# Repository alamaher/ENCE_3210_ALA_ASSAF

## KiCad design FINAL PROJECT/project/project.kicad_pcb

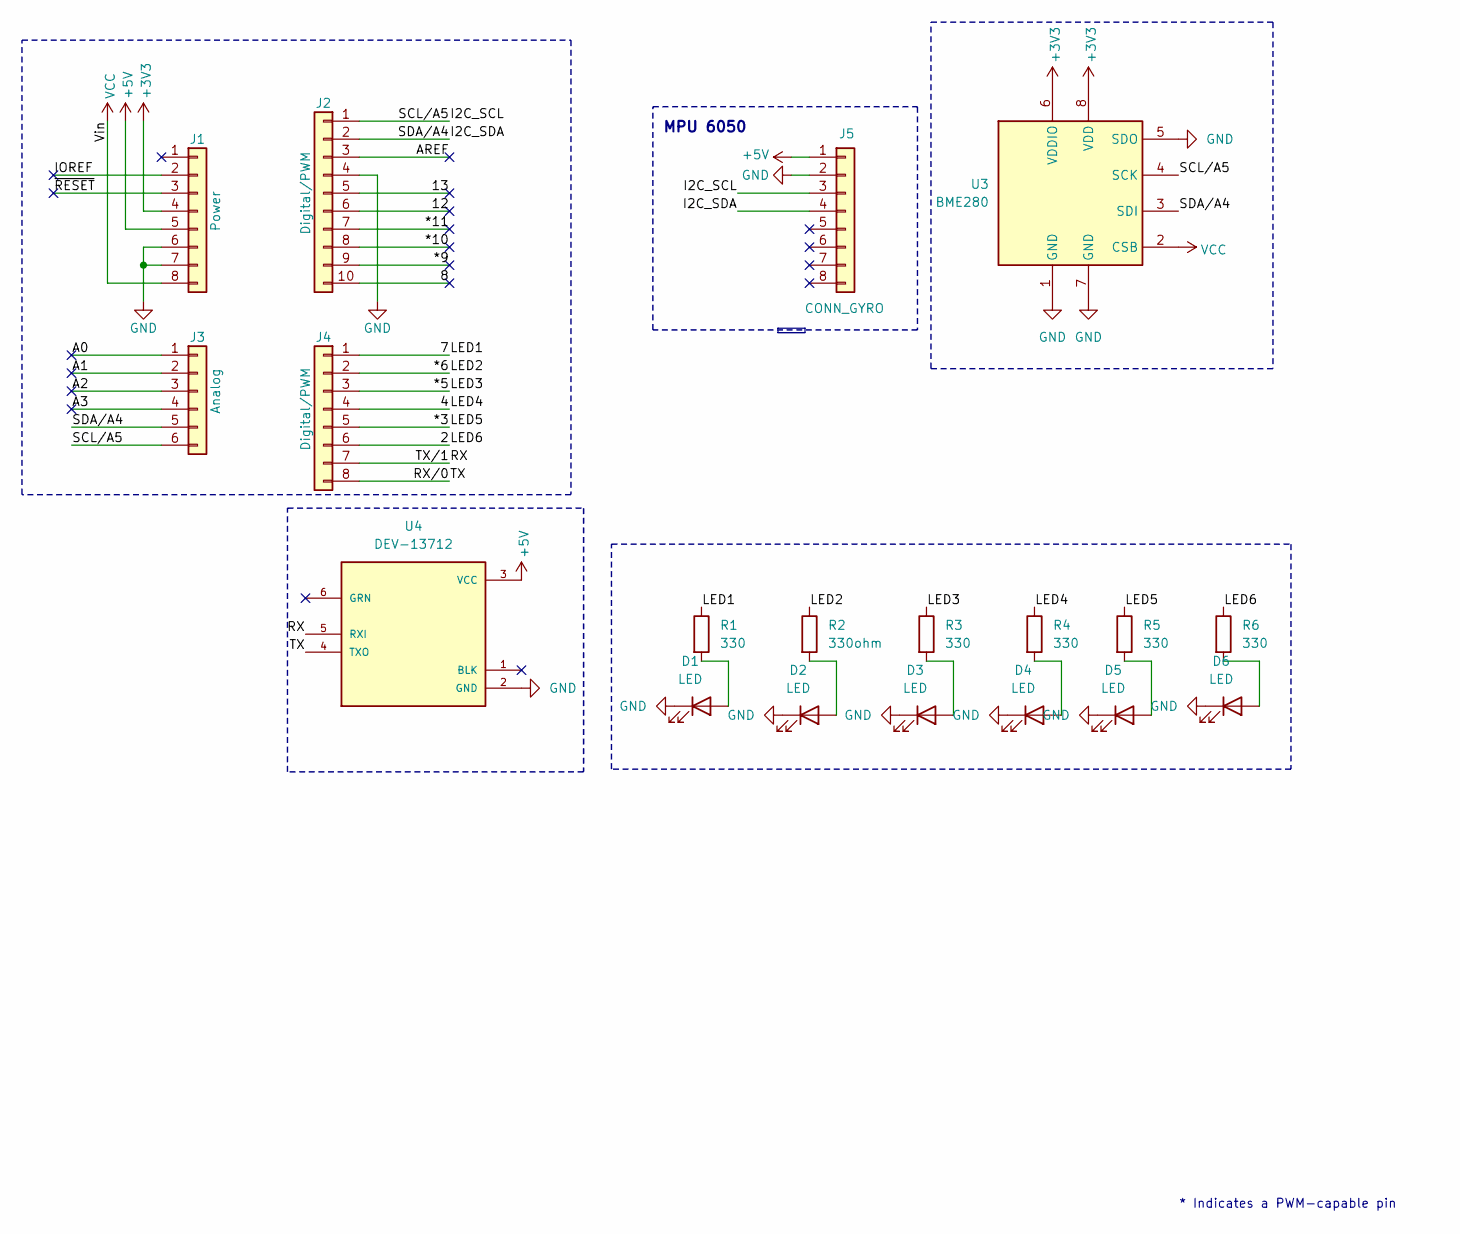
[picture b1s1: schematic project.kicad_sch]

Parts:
D1, D2, D3, D4, D5, D6: LED; LED_D5.0mm
J1: Power; PinSocket_1x08_P2.54mm_Vertical
J2: Digital/PWM; PinSocket_1x10_P2.54mm_Vertical
J3: Analog; PinSocket_1x06_P2.54mm_Vertical
J4: Digital/PWM; PinSocket_1x08_P2.54mm_Vertical
J5: CONN_GYRO; PinSocket_1x08_P2.54mm_Vertical
R1, R3, R4, R5, R6: 330; R_Axial_DIN0207_L6.3mm_D2.5mm_P10.16mm_Horizontal
R2: 330ohm; R_Axial_DIN0207_L6.3mm_D2.5mm_P10.16mm_Horizontal
U3: BME280; Bosch_LGA-8_2.5x2.5mm_P0.65mm_ClockwisePinNumbering
U4: DEV-13712; MODULE_DEV-13712; PARTREV v15

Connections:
+3V3: J1.4, U3.6 (VDDIO), U3.8 (VDD)
+5V: J1.5, J5.1, U4.3 (VCC)
/2: J4.6, R6.1
/4: J4.4, R4.1
/7: J4.1, R1.1
/8: J2.10
/12: J2.6
/13: J2.5
/*3: J4.5, R5.1
/*5: J4.3, R3.1
/*6: J4.2, R2.1
/*9: J2.9
/*10: J2.8
/*11: J2.7
/A0: J3.1
/A1: J3.2
/A2: J3.3
/A3: J3.4
/AREF: J2.3
/I2C_SCL: J2.1, J3.6, J5.3, U3.4 (SCK)
/I2C_SDA: J2.2, J3.5, J5.4, U3.3 (SDI)
/IOREF: J1.2
/RX: J4.7, U4.5 (RXI)
/RX/0: J4.8, U4.4 (TXO)
/~RESET: J1.3
GND: D1.1 (K), D2.1 (K), D3.1 (K), D4.1 (K), D5.1 (K), D6.1 (K), J1.6, J1.7, J2.4, J5.2, U3.1 (GND), U3.5 (SDO), U3.7 (GND), U4.2 (GND)
unnamed: D1.2 (A), R1.2
unnamed: D2.2 (A), R2.2
unnamed: D3.2 (A), R3.2
unnamed: D4.2 (A), R4.2
unnamed: D5.2 (A), R5.2
unnamed: D6.2 (A), R6.2
VCC: J1.8, U3.2 (CSB)

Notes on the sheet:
MPU 6050
* Indicates a PWM-capable pin

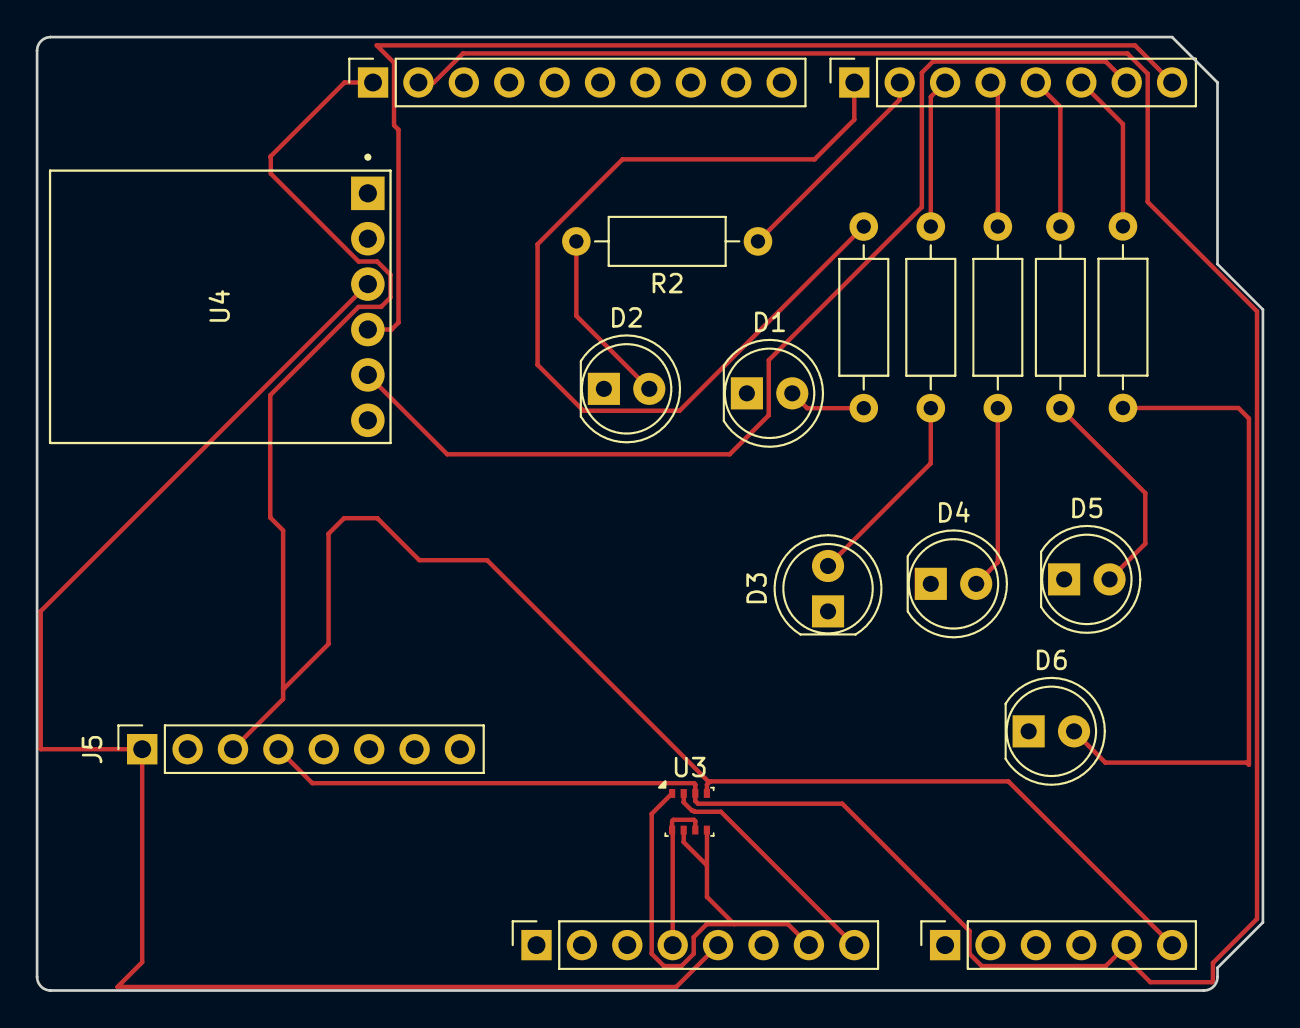
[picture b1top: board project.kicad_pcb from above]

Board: 2 copper layers, 68.6 x 53.3 mm, 19 parts (0 on the bottom side), 20 nets.

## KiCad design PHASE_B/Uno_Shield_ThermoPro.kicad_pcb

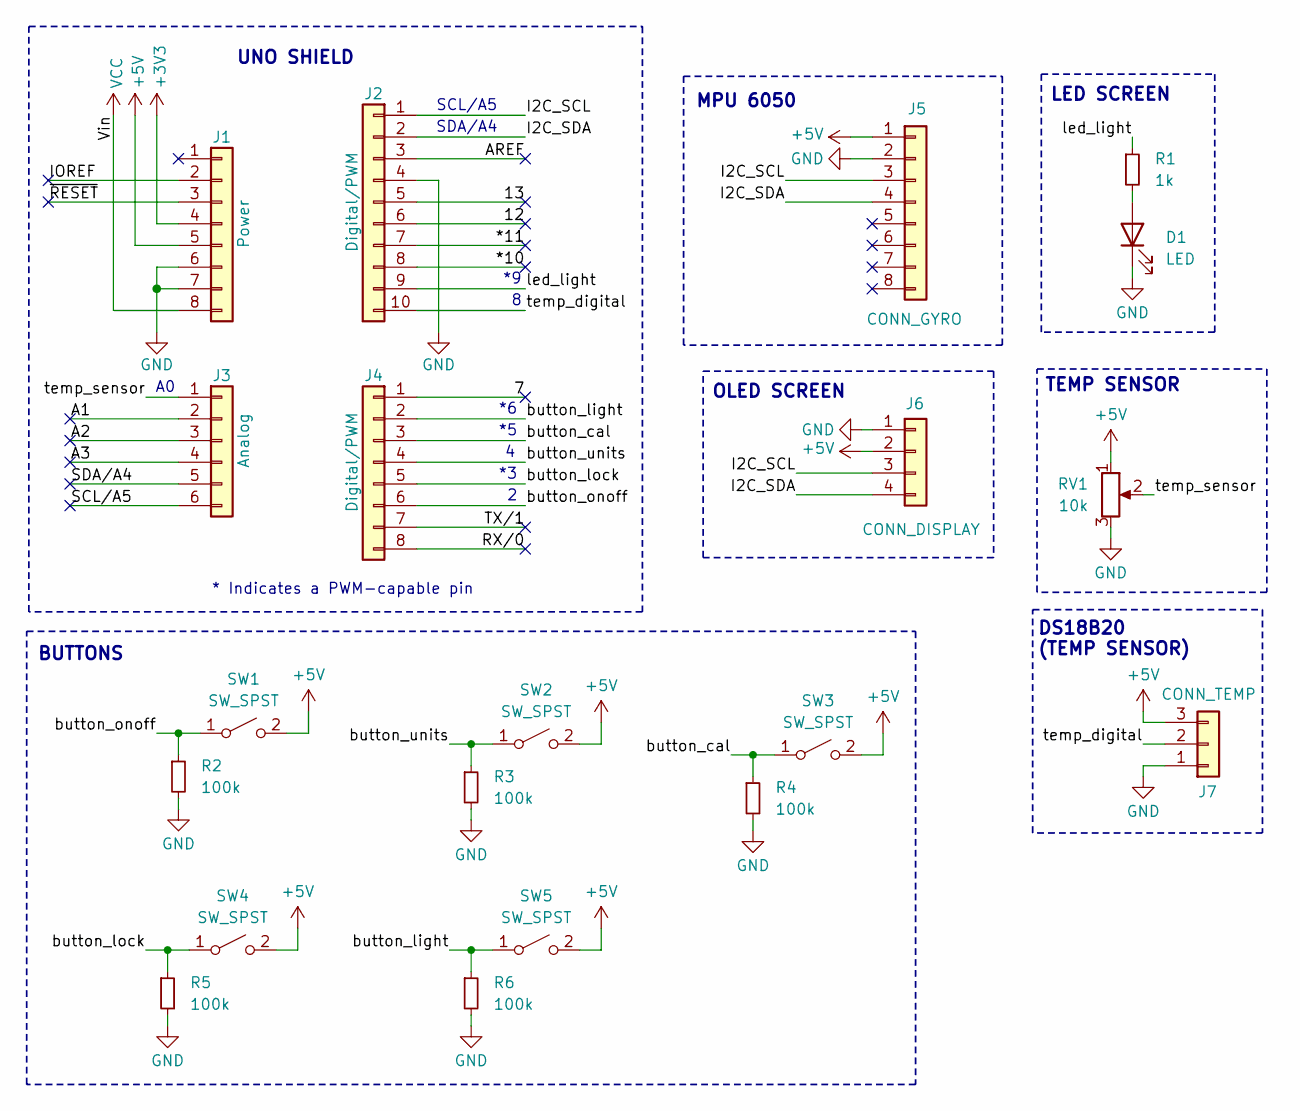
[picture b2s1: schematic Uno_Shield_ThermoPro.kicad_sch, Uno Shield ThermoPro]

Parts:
D1: LED; LED_D5.0mm
J1: Power; PinSocket_1x08_P2.54mm_Vertical
J2: Digital/PWM; PinSocket_1x10_P2.54mm_Vertical
J3: Analog; PinSocket_1x06_P2.54mm_Vertical
J4: Digital/PWM; PinSocket_1x08_P2.54mm_Vertical
J5: CONN_GYRO; PinSocket_1x08_P2.54mm_Vertical
J6: CONN_DISPLAY; PinSocket_1x04_P2.54mm_Vertical
J7: CONN_TEMP; JST_XH_B3B-XH-A_1x03_P2.50mm_Vertical
R1: 1k; R_Axial_DIN0207_L6.3mm_D2.5mm_P10.16mm_Horizontal
R2, R3, R4, R5, R6: 100k; R_Axial_DIN0207_L6.3mm_D2.5mm_P10.16mm_Horizontal
RV1: 10k; Potentiometer_Bourns_3386P_Vertical
SW1, SW2, SW3, SW4, SW5: SW_SPST; SW_PUSH_6mm

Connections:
+3V3: J1.4
+5V: J1.5, J5.1, J6.2, J7.3, RV1.1, SW1.2 (B), SW2.2 (B), SW3.2 (B), SW4.2 (B), SW5.2 (B)
/7: J4.1
/12: J2.6
/13: J2.5
/*10: J2.8
/*11: J2.7
/A1: J3.2
/A2: J3.3
/A3: J3.4
/AREF: J2.3
/I2C_SCL: J2.1, J5.3, J6.3
/I2C_SDA: J2.2, J5.4, J6.4
/IOREF: J1.2
/RX/0: J4.8
/SCL/A5: J3.6
/SDA/A4: J3.5
/TX/1: J4.7
/button_cal: J4.3, R4.1, SW3.1 (A)
/button_light: J4.2, R6.1, SW5.1 (A)
/button_lock: J4.5, R5.1, SW4.1 (A)
/button_onoff: J4.6, R2.1, SW1.1 (A)
/button_units: J4.4, R3.1, SW2.1 (A)
/led_light: J2.9, R1.1
/temp_digital: J2.10, J7.2
/temp_sensor: J3.1, RV1.2
/~RESET: J1.3
GND: D1.1 (K), J1.6, J1.7, J2.4, J5.2, J6.1, J7.1, R2.2, R3.2, R4.2, R5.2, R6.2, RV1.3
unnamed: D1.2 (A), R1.2
VCC: J1.8

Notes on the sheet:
DS18B20 (TEMP SENSOR)
OLED SCREEN
LED SCREEN
TEMP SENSOR
UNO SHIELD
MPU 6050
SCL/A5
SDA/A4
BUTTONS
* Indicates a PWM-capable pin

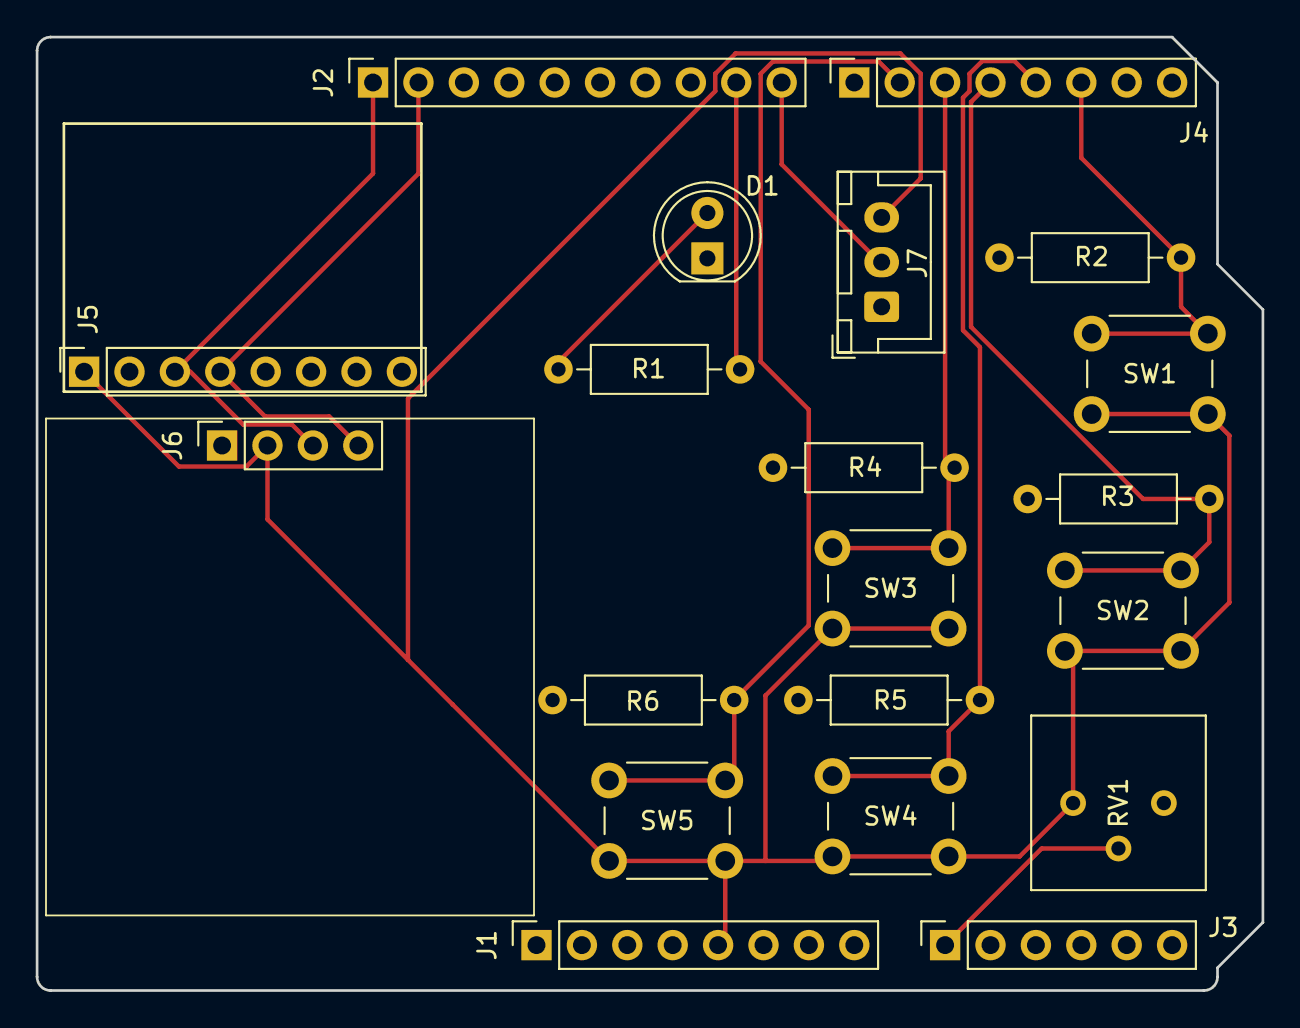
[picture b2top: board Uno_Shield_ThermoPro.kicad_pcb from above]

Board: 2 copper layers, 68.6 x 53.3 mm, 20 parts (0 on the bottom side), 13 nets.

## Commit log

2025-02-04 Uploaded kicad files
2025-02-04 uploaded lab 1
2025-03-06 hello
2025-03-10 updated solution
